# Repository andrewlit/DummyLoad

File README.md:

# Andrew's Electronic Load

This is a project to build a programmable electronic load. Currently it's rated for about 2A max but that could potentially be upgraded.

## Status

Currently, the project is in software development. The hardware is all done, though mostly untested. Software is coming along well though, and a beta version should hopefully be done soon. 

## Features

There are a number of features that will eventually make it into this project. The planned software versions are as follows:

### Version 0:

  * Navigation of the display via front panel knob
  * Able to set desired current
  * Display shows current, voltage, and power

### Version 1:

  * Specify cutoff voltage, for battery testing
  * Specify constant current or constant power
  * Monitor runtime, for battery testing

### Version 2:

  * Implement datalogging to SD card
  * (potential) place load profiles on SD card, to vary load over test duration

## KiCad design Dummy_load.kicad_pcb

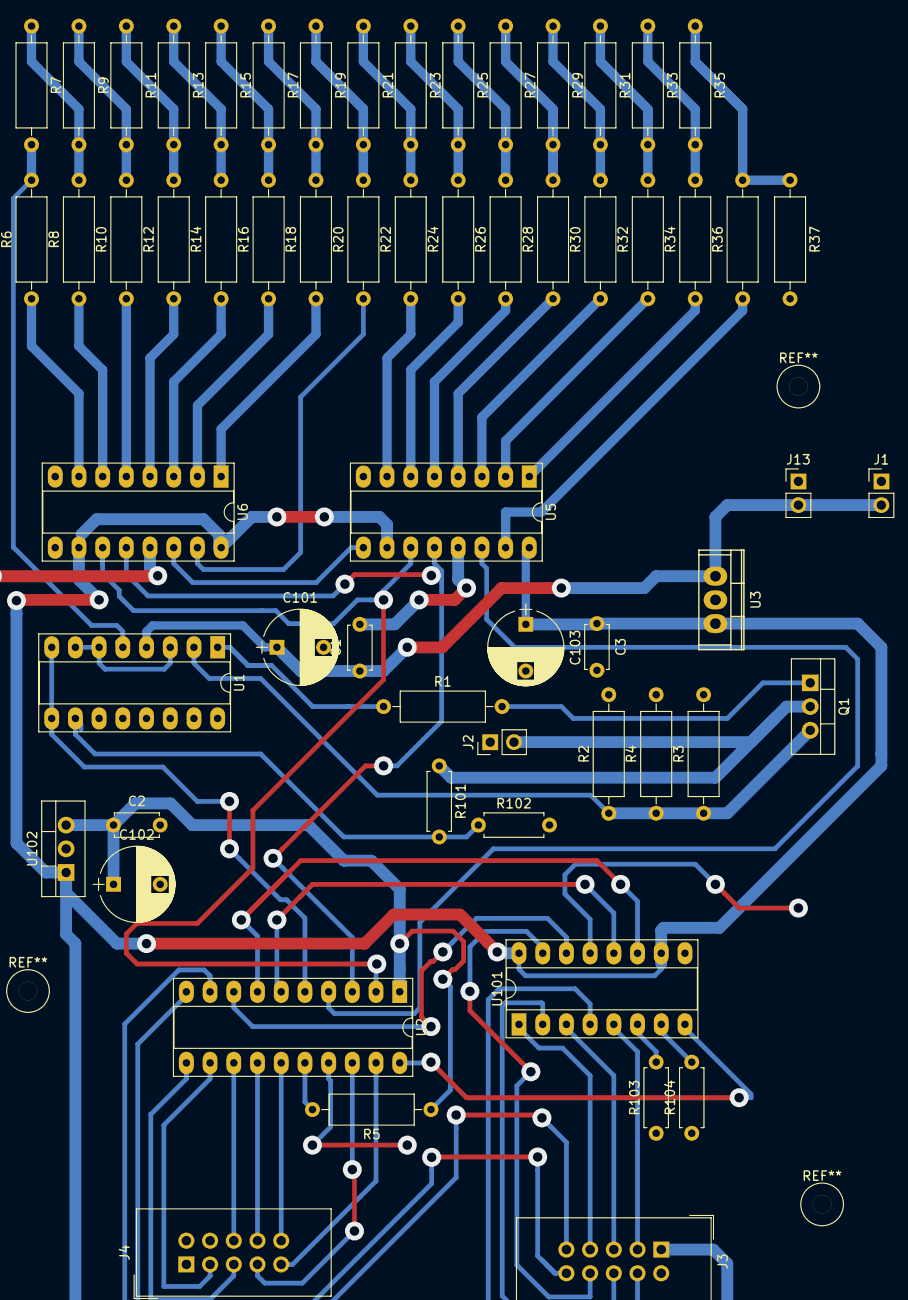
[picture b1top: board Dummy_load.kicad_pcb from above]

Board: 2 copper layers, 60 parts (0 on the bottom side), 68 nets.

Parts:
C1: 0.01uf; C_Disc_D4.7mm_W2.5mm_P5.00mm
C2, C3: .01uf; C_Disc_D4.7mm_W2.5mm_P5.00mm
C101, C102, C103: 6.8uF; CP_Radial_D8.0mm_P5.00mm
J1: TEST_2P; PinHeader_1x02_P2.54mm_Vertical
J2, J13: Conn_01x02; PinHeader_1x02_P2.54mm_Vertical
J3, J4: Conn_02x05_Odd_Even; IDC-Header_2x05_P2.54mm_Vertical
Q1: IRF601; TO-220-3_Vertical
R1, R7, R9, R11, R13, R15, R17, R19, R21, R23, R25, R27, R29, R31, R33, R35: 1K; R_Axial_DIN0309_L9.0mm_D3.2mm_P12.70mm_Horizontal
R2, R3, R4: 3R3; R_Axial_DIN0309_L9.0mm_D3.2mm_P12.70mm_Horizontal
R5: 47K; R_Axial_DIN0309_L9.0mm_D3.2mm_P12.70mm_Horizontal
R6, R8, R10, R12, R14, R16, R18, R20, R22, R24, R26, R28, R30, R32, R34, R36, R37: 2K; R_Axial_DIN0309_L9.0mm_D3.2mm_P12.70mm_Horizontal
R101: 6.8K; R_Axial_DIN0207_L6.3mm_D2.5mm_P7.62mm_Horizontal
R102, R103, R104: 1K; R_Axial_DIN0207_L6.3mm_D2.5mm_P7.62mm_Horizontal
U1: LM324; DIP-16_W7.62mm_Socket_LongPads
U2: MSP430G2553; DIP-20_W7.62mm_Socket_LongPads
U3: LM7805_TO220; TO-220
U5, U6, U101: 74HC595; DIP-16_W7.62mm_Socket_LongPads
U102: LM2936-3.3; TO-220-3_Vertical

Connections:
+3V3: C2.1, C102.1, R5.1, U2.1, U102.3
+7.5V: C1.1, C101.1, J1.2, J13.2, U1.4, U3.1
/r2r-16_DAC/DAC_OUT: R6.2, R7.2, U1.5
/r2r-16_DAC/SR_CLK: U2.2, U5.11, U6.11
/r2r-16_DAC/SR_LATCH: U2.3, U5.12, U6.12
/r2r-16_DAC/SR_SERIAL: U2.4, U5.14
GND: C1.2, C2.2, C3.2, C101.2, C102.2, C103.2, J1.1, J2.1, J3.2, J13.1, R2.2, R3.2, R4.2, R37.2, R102.2, R103.1, R104.1, U1.11, U2.17, U2.20, U3.2, U5.8, U5.13, U6.8, U6.13, U101.8, U101.13, U102.2
unnamed: J2.2, Q1.2, R101.1
unnamed: J3.3, U101.5
unnamed: J3.4, U101.4
unnamed: J3.5, U101.3
unnamed: J3.6, U101.2
unnamed: J3.7, U101.1
unnamed: J3.8, U101.15
unnamed: J3.9, U2.9
unnamed: J3.10, U2.10
unnamed: J4.3, U2.12
unnamed: J4.5, U2.11
unnamed: J4.6, U2.13
unnamed: J4.7, U2.18
unnamed: J4.8, U2.14
unnamed: J4.9, U2.19
unnamed: J4.10, U2.15
unnamed: Q1.1, R1.2
unnamed: Q1.3, R2.1, R3.1, R4.1, U1.2
unnamed: R1.1, U1.1
unnamed: R5.2, U2.16
unnamed: R6.1, U6.7
unnamed: R7.1, R8.2, R9.2
unnamed: R8.1, U6.6
unnamed: R10.1, U6.5
unnamed: R9.1, R10.2, R11.2
unnamed: R11.1, R12.2, R13.2
unnamed: R12.1, U6.4
unnamed: R13.1, R14.2, R15.2
unnamed: R14.1, U6.3
unnamed: R15.1, R16.2, R17.2
unnamed: R16.1, U6.2
unnamed: R17.1, R18.2, R19.2
unnamed: R18.1, U6.1
unnamed: R19.1, R20.2, R21.2
unnamed: R20.1, U6.15
unnamed: R21.1, R22.2, R23.2
unnamed: R22.1, U5.7
unnamed: R23.1, R24.2, R25.2
unnamed: R24.1, U5.6
unnamed: R25.1, R26.2, R27.2
unnamed: R26.1, U5.5
unnamed: R27.1, R28.2, R29.2
unnamed: R28.1, U5.4
unnamed: R29.1, R30.2, R31.2
unnamed: R30.1, U5.3
unnamed: R31.1, R32.2, R33.2
unnamed: R32.1, U5.2
unnamed: R33.1, R34.2, R35.2
unnamed: R34.1, U5.1
unnamed: R35.1, R36.2, R37.1
unnamed: R36.1, U5.15
unnamed: R101.2, R102.1, U1.10
unnamed: R103.2, U101.6
unnamed: R104.2, U101.7
unnamed: U1.3, U1.6, U1.7
unnamed: U1.8, U1.9, U2.5
unnamed: U5.9, U6.14
unnamed: U2.7, U101.11
unnamed: U2.6, U101.12
unnamed: U2.8, U101.14
VCC: C3.1, C103.1, J3.1, U3.3, U5.10, U5.16, U6.10, U6.16, U101.10, U101.16, U102.1

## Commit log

2018-01-17 On branch master
    Initial commit
2018-01-17 Added a comment to a file. On branch master Changes to be committed: modified: LoadCodeV1.ino
    Changes not staged for commit:
    modified: .LoadCodeV1.ino.un~
    modified: LoadCodeV1.ino~
2018-01-17 Experimenting experimenting experimenting
2018-01-17 Revert "Added a comment to a file."
    This reverts commit 7ac67644f99673c511daedfa0a2cfc5712bbc5de.
2018-01-17 Test commit for the test branch :)
2018-01-17 subtesting first commit
2018-01-17 I did a thing
    woot woop
2018-01-17 Testing from vim
2018-01-17 okay, now Vim is being used for the commits! On branch subtesting Changes to be committed: modified: .testing.swp modified: .testing.un~ modified: testing modified: testing~
2018-02-09 This is a branch to mess around with the library
    I'm not sure exactly what needs to be done, but it seems as though there
    is some issue with either the library or my configuration that is
    causing the display not to work. Hopefully this will help sort that out.
2018-02-10 Rotary encoder implemented, display manager 80%
    The display manager mostly works, except for stepping backwards through
    items and dealing with their values.
    Need to sort out an issue with moving back through the display elements;
    currently freaks TF out!
2018-02-10 Made a change to the CDLL
    I think it will fix the issue with the reverse traversing of the list
2018-02-10 She done goofed up
    Scroll kinda broken. Can go back a couple clicks and then it breaks, and
    you can go through the list of items twice before it breaks.
    Yeah.
2018-02-10 Fixed janky file structure
    Current status includes a very broken UI navigation system. You can
    scroll forwards through the list of items twice, then it locks up. You
    can also scroll backwards a tiny bit before it locks up. Pointer issue,
    probably. somewhere. ugh.
    At least the display is working now!
2018-02-10 More file structure fixes
    Turns out I forgot to rename some stuff, delete redundant stuff, etc
    etc. It's better now.
2018-02-10 Fixed encoder control issues
    Turns out it was the stupid serial commands that were still in there. I
    got that sorted out, and made a couple other tweaks. Next the overall
    display will have to be implemented.
2018-02-10 Trying to fix the display issues by streamlining
    Don't think this is gonna work though, the object oriented approach
    seems to be too heavy. This may need to be rebuilt almost from the
    ground up!
2018-02-10 Added .gitignore
2018-02-10 Added gitignore
2018-02-11 Eet iz vurkink! Vastly simplified the system
    Changed the display manager to a simple array based display system.
    Implemented the front panel button to disable the buzzer. Still need to
    implement the actual operation part, but interface wise it's mostly
    done.
2018-02-11 Updated gitignore to ignore swapfiles
2018-02-11 Deleted unnecessary DisplayManager file
    The improvements made to the display system made this file unneeded
2018-02-11 Added readme
2019-04-21 Adding sync to gogs
2019-04-21 Updated gitignore
